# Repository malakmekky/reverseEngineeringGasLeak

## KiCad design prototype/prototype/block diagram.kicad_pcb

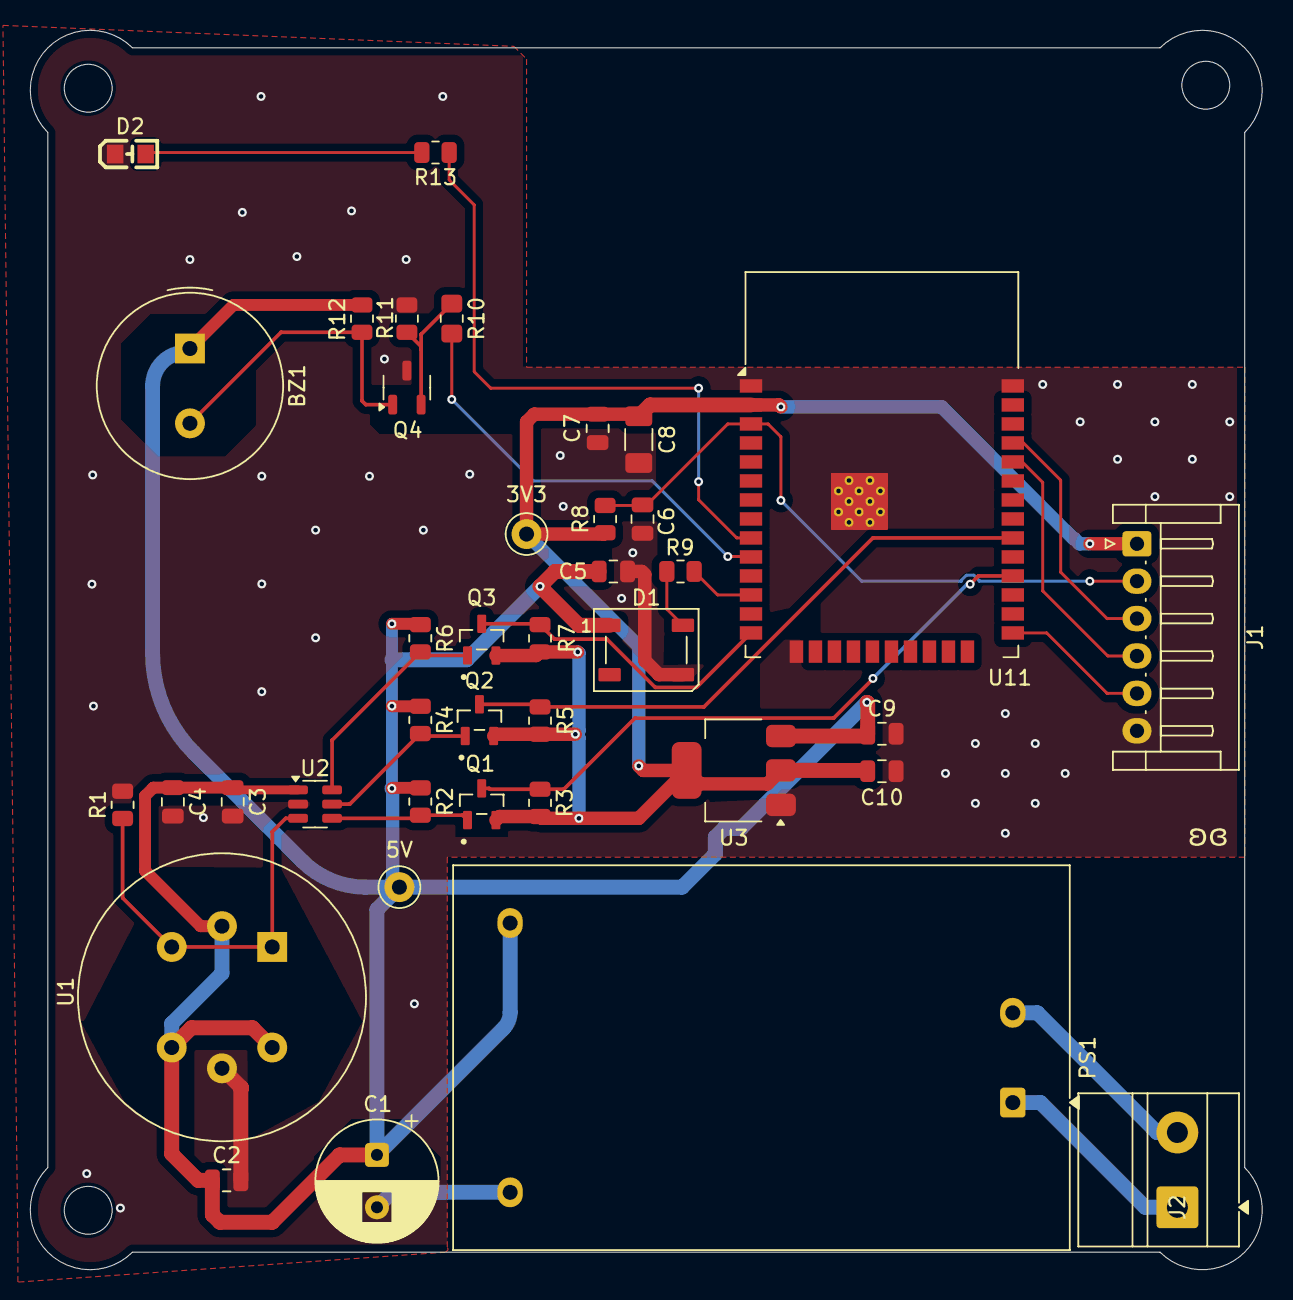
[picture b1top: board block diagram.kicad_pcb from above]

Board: 2 copper layers, 82.3 x 82.8 mm, 39 parts (0 on the bottom side), 23 nets.

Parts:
3V3: 3v3; TestPoint_Keystone_5000-5004_Miniature
5V: 5v; TestPoint_Keystone_5000-5004_Miniature
BZ1: Buzzer; Buzzer_TDK_PS1240P02BT_D12.2mm_H6.5mm
C1: 220uF; CP_Radial_D8.0mm_P3.50mm
C2, C9, C10: 10uF; C_0805_2012Metric
C3: 10nF; C_0805_2012Metric
C4, C6: 1uF; C_0805_2012Metric
C5, C7: 0.1uF; C_0805_2012Metric
C8: 22uF; C_1206_3216Metric_Pad1.33x1.80mm_HandSolder
D1: WS2812B; LED_WS2812B_PLCC4_5.0x5.0mm_P3.2mm
D2: LED; LED-SMD_L2.0-W1.25-RD-GREEN
J1: Conn_01x06_Pin; JST_EH_S6B-EH_1x06_P2.50mm_Horizontal
J2: Screw_Terminal_01x02; TerminalBlock_MetzConnect_Type011_RT05502HBLC_1x02_P5.00mm_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
PS1: HLK-5M05; Converter_ACDC_Hi-Link_HLK-5Mxx
Q1, Q2, Q3: 2N7002; SOT95P240X111-3N
Q4: AO3400; SOT-23-3
R1: 20k; R_0805_2012Metric
R2, R3, R4, R5, R6, R7: 4.7k; R_0805_2012Metric
R8, R11: 10k; R_0805_2012Metric
R9, R13: 330; R_0805_2012Metric
R10: 100; R_0805_2012Metric_Pad1.20x1.40mm_HandSolder
R12: 1k; R_0805_2012Metric
U1: MQ-5; MQ-6
U2: CI121S021 [adc]; SOT-23-6
U3: AMS1117-3.3; SOT-223-3_TabPin2
U11: ESP32-WROOM-32E; ESP32-WROOM-32D

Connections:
+3.3V: 3V3.1, C7.1, C8.1, C10.1, J1.1, Q1.2 (G), Q2.2 (G), Q3.2 (G), R3.1, R5.1, R7.1, R8.1, U3.2 (VO), U11.2 (VDD)
+5V: 5V.1, BZ1.1 (+), C1.1, C2.1, C3.1, C4.1, C5.1, C9.1, D1.1 (VDD), PS1.4 (+Vout), R2.1, R4.1, R6.1, R12.1, U1.2 (VH+), U1.4 (A2), U1.6 (A1), U2.1 (VA), U3.3 (VI)
/BUZZ_OUT: R10.2, U11.10 (IO25)
/CLK_3: Q1.3 (S), R3.2, U11.28 (IO17)
/CLK_5: Q1.1 (D), R2.2, U2.4 (SCLK)
/CS_3: Q3.3 (S), R7.2, U11.14 (IO12)
/CS_5: Q3.1 (D), R6.2, U2.6 (~CS)
/ESP_EN: C6.1, J1.2, R8.2, U11.3 (EN)
/ESP_IO0: J1.5, U11.25 (IO0)
/ESP_RXD0: J1.4, U11.34 (RXD0/IO3)
/ESP_TXD0: J1.3, U11.35 (TXD0/IO1)
/IO_16_on: R13.1, U11.9 (IO33)
/L: J2.1, PS1.1 (AC/L)
/N: J2.2, PS1.2 (AC/N)
/SDATA_3: Q2.3 (S), R5.2, U11.30 (IO18)
/SDATA_5: Q2.1 (D), R4.2, U2.5 (SDATA)
/STATUS_LED: R9.1, U11.12 (IO27)
/Sensor_A_O: R1.1, U1.1 (B1), U1.3 (B2), U2.3 (VIN)
GND: C1.2, C2.2, C3.2, C4.2, C5.2, C6.2, C7.2, C8.2, C9.2, C10.2, D1.3 (VSS), D2.1 (K), J1.6, PS1.3 (-Vout), Q4.3 (S), R1.2, R11.2, U1.5 (VH-), U2.2 (GND), U3.1 (GND), U11.1 (GND), U11.15 (GND), U11.38 (GND), U11.39 (GND)
unnamed: BZ1.2 (-), Q4.1 (D), R12.2
unnamed: D1.4 (DIN), R9.2
unnamed: D2.2 (A), R13.2
unnamed: Q4.2 (G), R10.1, R11.1

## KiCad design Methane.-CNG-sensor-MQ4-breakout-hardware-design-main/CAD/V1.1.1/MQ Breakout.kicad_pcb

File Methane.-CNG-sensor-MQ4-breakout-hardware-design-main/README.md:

# Methane, CNG sensor MQ4 breakout Hardware Design

## About the Product

|  |
| :----------------------------------------------------------: |
| [Buy Methane, CNG sensor MQ4 breakout](https://www.solde.red/333104) |

Have you ever wondered how much natural gas and methane are in your living room? You can easily measure that! The MQ4 breakout board is a simple-to-use sensor that detects the natural gas and methane (CH4) in the air. Once heated to working temperature, it detects changes in air concentrations very quickly between 200 and 10000 ppm.

On the through-holes, the DO stands for digital out and AO for analog out. The digital output is obtained by setting a threshold value using the potentiometer. The analog output will depend on the intensity of the gas around the sensor.

---

## Repository Contents

This repository contains all design files for Methane, CNG sensor MQ4 breakout, organized as follows:

- **`CAD` folder**: Contains KiCAD design files, including:
  - Schematics
  - PCB layout
  - Panel PCB layout
  - Source 3D files in Fusion360, if any
  - All files are sorted by version with a detailed change log.
- **`OUTPUTS` folder**: Includes all production-ready files, such as:
  - Bill of Materials (BOM) and interactive BOM (iBOM)
  - PDF versions of schematics
  - 3D `.step` file of the board
  - 3D-printable models
  - Gerber files for PCB manufacturing
  - Image of the pinout of the board
  - Product image
  - Compliance, legal and generic sales documents

Refer to the `Change Log` in the CAD folder for details about updates between versions.

---

## Learn More About the Product

Beyond the repository, explore the following resources:

### Soldered Verify

The **Soldered Verify** system ensures every board you purchase from Soldered is fully functional. It also provides access to exclusive test data for your product. To get started, find the unique Soldered Verify ID on your product's packaging and enter the ID on the [Soldered Verify page](https://soldered.com/verify/) to access test results and additional product details.

### Soldered Community

Soldered Community is your go-to place for technical support. Our engineers track and answer all questions posted there, and it’s a great space for the maker community. Get answers to your questions and solutions for your challenges at [Soldered Community](https://soldered.com/community).

### solde.red

solde.red is an ultimate URL shortener and information hub. Access it by typing solde.red/ followed by your product SKU, e.g., [solde.red/333000](https://solde.red/333000), to find getting-started guides, datasheets, open-source hardware and software files, certifications, images, pinouts, and more. Read more about the shortener [here](https://solde.red/info/).

---

## Contributing

Contributions are welcome! Here’s how you can get involved:

- Submit pull requests to enhance the design or fix issues.
- Report bugs or problems by opening an issue.

We encourage community collaboration to make this product even better.

---

## About Soldered

[Soldered for Makers](https://soldered.com) specializes in designing and manufacturing electronic products tailored for enthusiasts, ranging from hobbyists to professionals. Our portfolio includes electronic boards, sensors, and actuators that are widely utilized in fields such as microelectronics, mechatronics, robotics, programming, and IoT. Every product we offer is designed in-house and built upon open-source hardware and software platforms. Proudly certified and manufactured within the European Union, our catalog likely includes the product you need for your project.

We complement these products with comprehensive tutorials and manuals, product descriptions, schematics, programming codes, and project examples. Our round-the-clock [customer and technical support](https://soldered.com/community) is available for all our products, irrespective of the sales channel. Soldered’s success and services reflect our maker community’s unwavering [trust](https://www.trustpilot.com/review/soldered.com), for which we are deeply grateful. Join our community and create using Soldered products.

---

## License

All Soldered open-source hardware (OSH) is under The TAPR Open Hardware License. Read more in the LICENSE file located in this repository.

**Disclaimer:**

No warranty - all designs in this repository are distributed in the hope that they will be useful, but without any warranty. They are provided "AS IS", therefore without warranty of any kind, either expressed or implied. The entire quality and performance of what you do with the contents of this repository are your responsibility. In no event Soldered Electronics will be liable for your damages, or losses, including any general, special, incidental, or consequential damage arising out of the use or inability to use the contents of this repository. 

---

## Have fun!

Thank you for your support from your fellow makers at Soldered Electronics.

Happy Making!

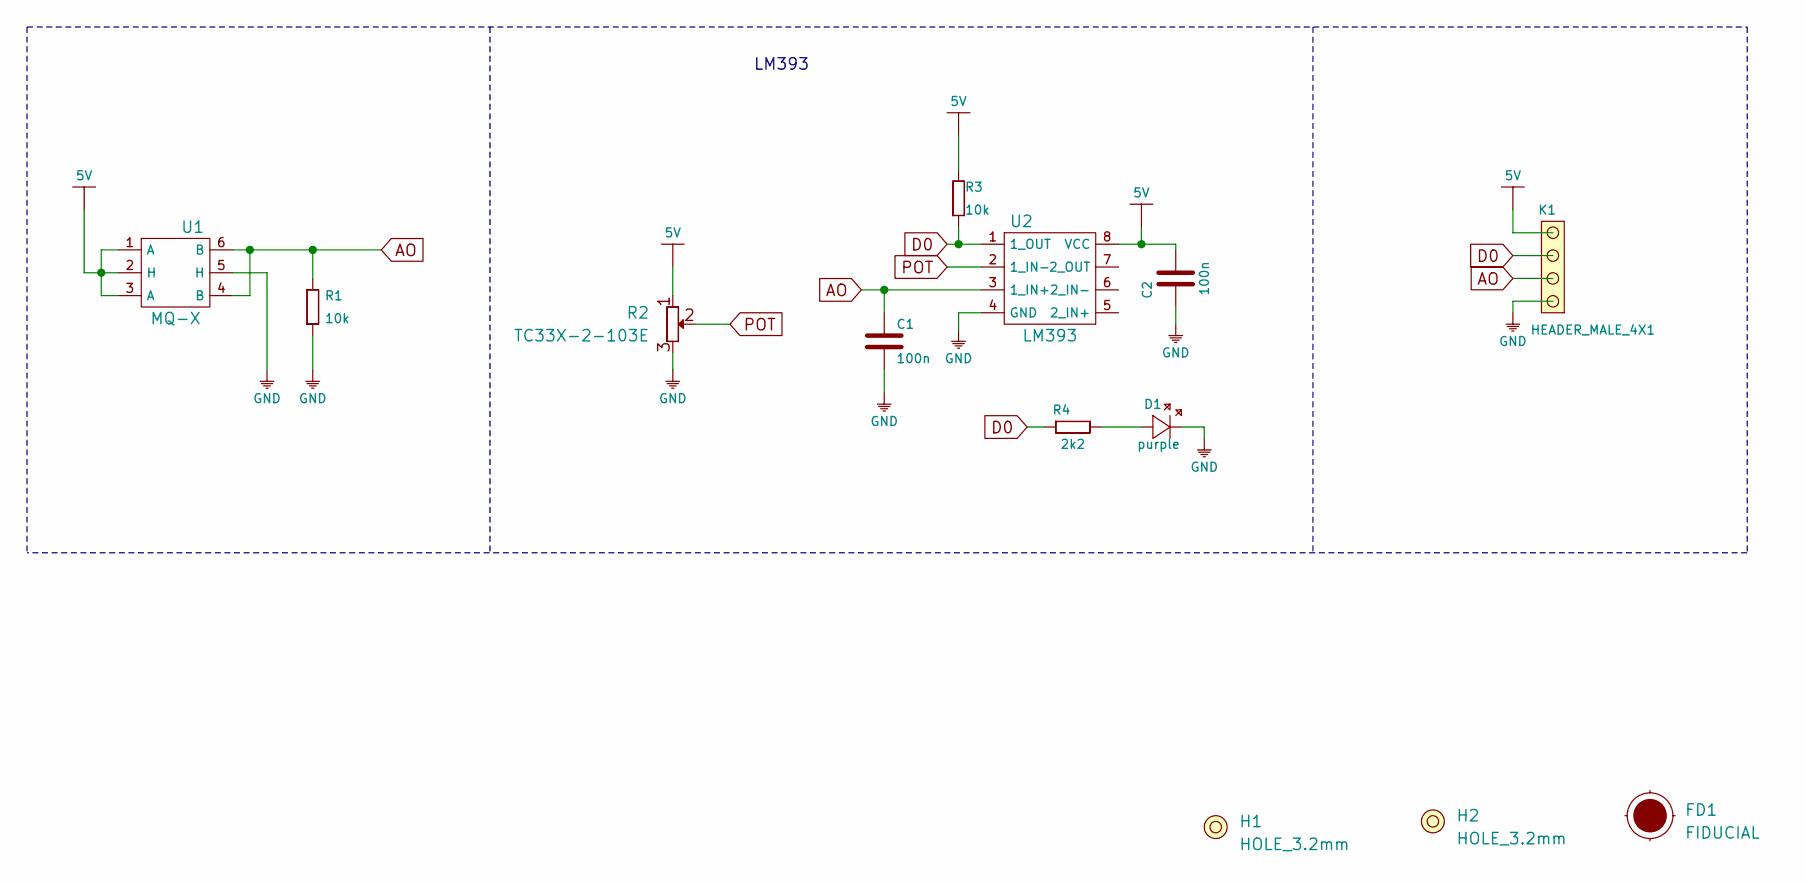
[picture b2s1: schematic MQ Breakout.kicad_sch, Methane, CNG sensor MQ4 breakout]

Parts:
C1, C2: 100n; 0603C
D1: purple; 0402LED
FD1: FIDUCIAL; FIDUCIAL_23
H1, H2: HOLE_3.2mm
K1: HEADER_MALE_4X1
R1, R3: 10k; 0603R
R2: TC33X-2-103E; tc33x-2-103e
R4: 2k2; 0402R
U1: MQ-X; MQ
U2: LM393; SOIC−8

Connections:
5V: C2.2, K1.4, R2.1, R3.2, U1.1 (A), U1.2 (H), U1.3 (A), U2.8 (VCC)
AO: C1.2, K1.2, R1.2, U1.4 (B), U1.6 (B), U2.3 (1_IN+)
D0: K1.3, R3.1, R4.1, U2.1 (1_OUT)
GND: C1.1, C2.1, D1.2 (K), K1.1, R1.1, R2.3, U1.5 (H), U2.4 (GND)
unnamed: D1.1 (A), R4.2
POT: R2.2, U2.2 (1_IN-)

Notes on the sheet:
LM393

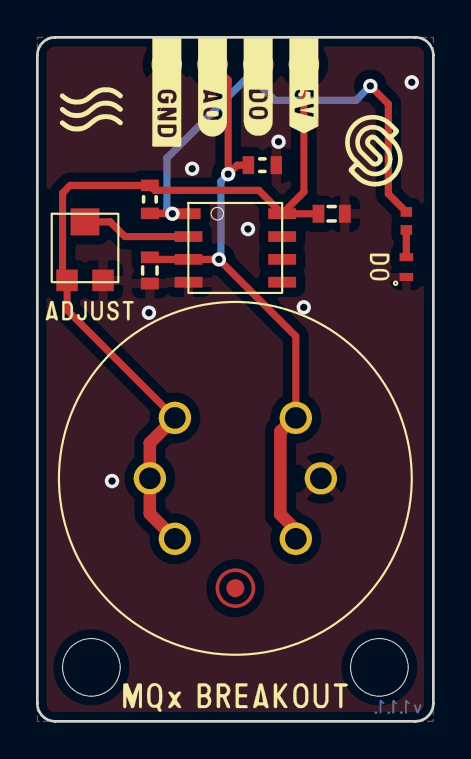
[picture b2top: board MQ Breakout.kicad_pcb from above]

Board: 2 copper layers, 22.0 x 38.0 mm, 13 parts (1 on the bottom side), 6 nets.

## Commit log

2026-01-14 malak farid tweakout at night
2026-01-14 fixed recovered
2026-01-15 thursday 15th
2026-01-17 saturday 17th
2026-01-18 sunday - simplified block
2026-01-19 monday - start of prototype simplified schematic
2026-01-19 added to do list
2026-01-20 edited the connections of the 220-5 (added the RLC) and added RLC for en pullup and 3v3 of esp
2026-01-20 updated overall schematic, should be done [will be checked]
2026-01-20 Renaming and creating folders to organize
    created folders, renamed block diagram to prototype and created folder for all RE
2026-01-21 cleaning up schematic of prototype
2026-01-21 cleaning up schematic of prototype complete
2026-01-22 final schematic organized
2026-01-22 updated footprints
2026-01-22 pcb layout and updated led
2026-01-23 pcb layout almost complete
2026-01-23 editing pcb layout (desktop)
2026-01-24 finished pcb prototype
2026-01-25 FINAL FINAL PCB
2026-01-25 FINAL FINAL PCB TO BE SENT
2026-01-28 final final pcb ever fr ong
2026-02-08 final pcb layout <3
